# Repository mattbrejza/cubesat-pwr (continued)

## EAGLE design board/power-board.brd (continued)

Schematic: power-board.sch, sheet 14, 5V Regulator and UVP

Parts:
C104, C110: 10n; C0603
C105: 100n; C0603
C106: 10u; C1206
C107: 0.1u; C0603
C108: 3.3n; C0603
C109: 22u; C1210
L2: 2.2u; VISHAY-INDUCTOR
R102: 14.5k; R0603
R103: 10.2k; R0603
R104: 12.4k; R0603
R105: 124k; R0603
R106, R107: 100k; R0603
R108: 0; R0603
R141: 4.02k; R0603
TP14, TP20: PTR1TP09R; TP09R
U46: TLV3491AIDBV; SOT23-5
U47: TPS62133RGT; RGT.16
U48: FDS8858CZ; SO8

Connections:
GND: C104.2, C105.2, C106.2, C107.2, C108.1, C109.2, C110.2, R103.1, R105.1, U46.2 (V-), U47.5 (FB), U47.6 (AGND), U47.8 (DEF), U47.15 (PGND), U47.16 (PGND), U47.PAD (AGND), U48.1 (S); also elsewhere on the board
unnamed: C108.2, U47.9 (SS/TR)
unnamed: L2.1, U47.1 (SW), U47.2 (SW), U47.3 (SW)
unnamed: R107.2, R108.2, U48.4 (G)
unnamed: R102.2, R103.2, R141.1
unnamed: R106.1, R141.2, U46.3 (+IN)
unnamed: R108.1, U48.7 (D), U48.8 (D)
unnamed: R104.1, R105.2, U46.4 (-IN)
REG3V3: C105.1, R104.2, U46.5 (V+); also elsewhere on the board
REG5V: C109.1, C110.1, L2.2, R107.1, TP20.TP, U47.7 (FSW), U47.14 (VOS), U48.3 (S); also elsewhere on the board
UVP5V_GATE: R106.2, TP14.TP, U46.1 (OUT), U48.2 (G)
UVP5V_OUT: U48.5 (D), U48.6 (D); also elsewhere on the board
VBATT: C104.1, C106.1, C107.1, R102.1, U47.10 (AVIN), U47.11 (PVIN), U47.12 (PVIN), U47.13 (EN); also elsewhere on the board

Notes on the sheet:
Application circuits taken from TPS62130 Datasheet Fig. 44.
FSW = High for 1.25MHz operation. Connect FSW to VOUT or PG.
See Fig. 50 for layout
3A Buck Regulators
TLV3491 bypass
5V Regulator and UVP

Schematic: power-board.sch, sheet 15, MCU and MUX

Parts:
C111, C113: 0.1u; C0603K
C112: 1n; C0603K
R29, R30: 4k7; R0603
R109: 47k; R0603
U49: MSP430F2132; RHB32
U50: ADG732; LFCSP48
X1: 32.768k; CC7V-T1A

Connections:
BATT_I2C_SCL: R30.1, U49.11; also elsewhere on the board
BATT_I2C_SDA: R29.1, U49.10; also elsewhere on the board
CHARGE_CSENSE_MUX: U50.27 (S19); also elsewhere on the board
GND: C111.2, C112.2, C113.2, U49.1, U49.TP (33), U50.20 (!CS), U50.21 (!WR), U50.22 (!EN), U50.23 (GND), U50.24 (VSS), U50.EXP (GND); also elsewhere on the board
MCU_INT: U49.15; also elsewhere on the board
MCU_RX: U49.14; also elsewhere on the board
MCU_TX: U49.13; also elsewhere on the board
MPPT2_LOWER_PV_VSENSE: U50.30 (S22); also elsewhere on the board
MPPT2_MID_PV_VSENSE: U50.31 (S23); also elsewhere on the board
MPPT_BUS_VSENSE: U50.29 (S21); also elsewhere on the board
MSP-RST: C112.1, R109.1, U49.5; also elsewhere on the board
MSP-TEST: U49.29; also elsewhere on the board
MUX_A0: U49.32, U50.15 (A0)
MUX_A1: U49.18, U50.16 (A1)
MUX_A2: U49.8, U50.17 (A2)
MUX_A3: U49.7, U50.18 (A3)
MUX_A4: U49.6, U50.19 (A4)
MUX_OUT: U49.16, U50.43 (D)
unnamed: U49.2, X1.P$2 (2)
unnamed: U49.3, X1.P$1 (1)
OCP1_CSENSE_MUX: U50.38 (S30); also elsewhere on the board
OCP1_MCU_EN: U49.23; also elsewhere on the board
OCP1_VSENSE: U50.46 (S15); also elsewhere on the board
OCP2_CSENSE_MUX: U50.48 (S13); also elsewhere on the board
OCP2_MCU_EN: U49.22; also elsewhere on the board
OCP2_VSENSE: U50.47 (S14); also elsewhere on the board
OCP3_CSENSE_MUX: U50.4 (S9); also elsewhere on the board
OCP3_MCU_EN: U49.21; also elsewhere on the board
OCP3_VSENSE: U50.3 (S10); also elsewhere on the board
OCP4_CSENSE_MUX: U50.7 (S6); also elsewhere on the board
OCP4_MCU_EN: U49.26; also elsewhere on the board
OCP4_VSENSE: U50.6 (S7); also elsewhere on the board
OCP5_CSENSE_MUX: U50.10 (S3); also elsewhere on the board
OCP5_MCU_EN: U49.25; also elsewhere on the board
OCP5_VSENSE: U50.5 (S8); also elsewhere on the board
OCP6_CSENSE_MUX: U50.9 (S4); also elsewhere on the board
OCP6_MCU_EN: U49.24; also elsewhere on the board
OCP6_VSENSE: U50.8 (S5); also elsewhere on the board
PV_EAST1_CSENSE_MUX: U50.40 (S32); also elsewhere on the board
PV_EAST2_CSENSE_MUX: U50.39 (S31); also elsewhere on the board
PV_NORTH1_CSENSE_MUX: U50.26 (S18); also elsewhere on the board
PV_NORTH2_CSENSE_MUX: U50.25 (S17); also elsewhere on the board
PV_SOUTH1_CSENSE_MUX: U50.34 (S26); also elsewhere on the board
PV_SOUTH2_CSENSE_MUX: U50.33 (S25); also elsewhere on the board
PV_TOP1_CSENSE_MUX: U50.12 (S1); also elsewhere on the board
PV_TOP2_CSENSE_MUX: U50.11 (S2); also elsewhere on the board
PV_WEST1_CSENSE_MUX: U50.28 (S20); also elsewhere on the board
PV_WEST2_CSENSE_MUX: U50.32 (S24); also elsewhere on the board
SYS_3V3_CSENSE_MUX: U50.1 (S12); also elsewhere on the board
SYS_5V_CSENSE_MUX: U50.2 (S11); also elsewhere on the board
UVP3V3_OUT: C111.1, C113.1, R29.2, R30.2, R109.2, U49.30, U50.13 (VDD), U50.14 (VDD); also elsewhere on the board
UVP3V3_VSENSE: U50.36 (S28); also elsewhere on the board
UVP5V_VSENSE: U50.35 (S27); also elsewhere on the board
VBATT_VSENSE: U50.37 (S29); also elsewhere on the board

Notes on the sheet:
Decoupling
Microcontroller and Multiplexer

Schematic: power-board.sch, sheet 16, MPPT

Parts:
C114, C115, C122, C123, C145, C146, C150, C151, C155, C156, C160, C161: 10u; C0805K
C116, C117, C144, C149, C154, C159: 100n; C0603K
C118, C119, C143, C148, C153, C158: 1u; C0603K
C120, C121, C147, C152, C157, C162: 4.7u; C0805K
D7, D8, D12, D13, D14, D15: 5V1; SMBJ
L3, L4, L6, L7, L8, L9: 10uH; MSS7341
R110, R111, R112, R113, R114, R115, R118, R119, R143, R144, R145, R147, R148, R149, R151, R152, R153, R155: 1k; R0603
R116, R117, R142, R146, R150, R154: 10m; R1206
TP29, TP31, TP32, TP33, TP35: PTR1TP09R; TP09R
U51, U52, U55, U56, U57, U58: SPV1040T; TSSOP8

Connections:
CHARGE_IN: C122.1, C145.1, C155.1, R113.1, R116.1, R119.1, R142.1, R149.1, R150.1, TP31.TP; also elsewhere on the board
GND: C115.2, C117.2, C121.2, C123.2, C149.2, C150.2, C151.2, C152.2, C159.2, C160.2, C161.2, C162.2, D8.A, D13.A, D15.A, TP33.TP, U52.2 (GND), U52.5 (VCTRL), U56.2 (GND), U56.5 (VCTRL), U58.2 (GND), U58.5 (VCTRL); also elsewhere on the board
MPPT1H_PV_P: C114.1, L3.1, R110.1; also elsewhere on the board
MPPT1L_PV_P: C115.1, L4.1, R111.1; also elsewhere on the board
MPPT1_MID: C114.2, C116.2, C120.2, C122.2, C123.1, D7.A, R115.1, R117.1, TP29.TP, U51.2 (GND), U51.5 (VCTRL); also elsewhere on the board
MPPT2H_PV_P: C146.1, L6.1, R143.1; also elsewhere on the board
MPPT2L_PV_P: C151.1, L7.1, R147.1; also elsewhere on the board
MPPT2_MID: C144.2, C145.2, C146.2, C147.2, C150.1, D12.A, R145.1, R146.1, TP32.TP, U55.2 (GND), U55.5 (VCTRL); also elsewhere on the board
MPPT3H_PV_P: C156.1, L8.1, R151.1; also elsewhere on the board
MPPT3L_PV_P: C161.1, L9.1, R155.1; also elsewhere on the board
MPPT3_MID: C154.2, C155.2, C156.2, C157.2, C160.1, D14.A, R153.1, R154.1, TP35.TP, U57.2 (GND), U57.5 (VCTRL); also elsewhere on the board
unnamed: C118.1, R112.2, U51.7 (ICTRL+)
unnamed: C118.2, R113.2, U51.6 (ICTRL-)
unnamed: C120.1, D7.C, R112.1, R116.2, U51.4 (VOUT)
unnamed: C116.1, R110.2, U51.1 (MPP-SET), U51.8 (XSHUT)
unnamed: L3.2, U51.3 (LX)
unnamed: C143.1, R118.2, U55.7 (ICTRL+)
unnamed: C143.2, R119.2, U55.6 (ICTRL-)
unnamed: C147.1, D12.C, R118.1, R142.2, U55.4 (VOUT)
unnamed: C119.1, R114.2, U52.7 (ICTRL+)
unnamed: C119.2, R115.2, U52.6 (ICTRL-)
unnamed: C121.1, D8.C, R114.1, R117.2, U52.4 (VOUT)
unnamed: C117.1, R111.2, U52.1 (MPP-SET), U52.8 (XSHUT)
unnamed: L4.2, U52.3 (LX)
unnamed: C144.1, R143.2, U55.1 (MPP-SET), U55.8 (XSHUT)
unnamed: L6.2, U55.3 (LX)
unnamed: C148.1, R144.2, U56.7 (ICTRL+)
unnamed: C148.2, R145.2, U56.6 (ICTRL-)
unnamed: C152.1, D13.C, R144.1, R146.2, U56.4 (VOUT)
unnamed: C149.1, R147.2, U56.1 (MPP-SET), U56.8 (XSHUT)
unnamed: L7.2, U56.3 (LX)
unnamed: C153.1, R148.2, U57.7 (ICTRL+)
unnamed: C153.2, R149.2, U57.6 (ICTRL-)
unnamed: C157.1, D14.C, R148.1, R150.2, U57.4 (VOUT)
unnamed: C154.1, R151.2, U57.1 (MPP-SET), U57.8 (XSHUT)
unnamed: L8.2, U57.3 (LX)
unnamed: C158.1, R152.2, U58.7 (ICTRL+)
unnamed: C158.2, R153.2, U58.6 (ICTRL-)
unnamed: C162.1, D15.C, R152.1, R154.2, U58.4 (VOUT)
unnamed: C159.1, R155.2, U58.1 (MPP-SET), U58.8 (XSHUT)
unnamed: L9.2, U58.3 (LX)

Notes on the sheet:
MPPT
MPPT 1H
MPPT 1L
MPPT 2L
MPPT 3L
MPPT 3H
MPPT 2H
north/south
east/west
top

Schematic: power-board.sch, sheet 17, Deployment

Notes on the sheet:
Deployment power MOSFETs
I think this should be connected to the GND, not to RBF_A

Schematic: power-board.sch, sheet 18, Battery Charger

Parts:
C124: 2.2u; C1210
C125: C0603; P0603
C126, C127, C130, C139: 1.0u; P0805
C128, C141: 22p; P0603
C129, C132, C142: 0.1u; P0603
C131: 100n; P0603
C133, C140: 10u; C1210
C134: 1.0u; C0805
C135: C-EUC0603; C0603
C137: 10u; P1210
D9, D11: PDS1040; POWERDI5
D10: ZLLS350; SOD-523
L5: IHLP2525CZ
Q3: SI7288; SO8-POWERPAK_DUAL
R120, R121: 3.9; R0603
R122: 10.0k; P0603
R123: 30.1k; P0603
R124: 5.23k; P0603
R125: 100; P0603
R126, R130: 100k; P0603
R127: 10; P0805
R128, R133: R0805; P0805
R129: 698k; P0603
R131: 2.2; P0603
R134: 62m; R1206
R135, R137: 0; P0603
R138: 301k; P0603
R139: 102k; P0603
SH1, SH2: SHORT
U53: BQ24650_RVA_16; RVA16_2P14X2P14

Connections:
CHARGE_BATT: C142.1, R137.2; also elsewhere on the board
CHARGE_IN: C128.1, D9.LEFT (A1), D9.RIGHT (A2), R120.2, R121.2, R129.2; also elsewhere on the board
CHARGE_OUT: C137.1, C139.1, D11.LEFT (A1), D11.RIGHT (A2), R134.2, R135.2; also elsewhere on the board
GND: C124.2, C125.2, C126.2, C127.1, C130.2, C131.2, C133.2, C134.2, C137.2, C139.2, C140.2, C142.2, Q3.3 (S), R122.1, R123.1, R126.1, R130.1, R133.1, R139.1, SH1.1, SH1.2, SH2.1, SH2.2, U53.11 (GND), U53.17 (EPAD); also elsewhere on the board
MPPSET: C128.2, R129.1, R130.2, U53.2 (MPPSET)
unnamed: C141.1, R137.1, R138.2
unnamed: C124.1, R120.1, R121.1
unnamed: C135.2, R133.2
unnamed: C127.2, R127.1, R128.1, U53.1 (VCC)
unnamed: C130.1, D10.2 (A), U53.12 (REGN)
unnamed: C129.1, C131.1, L5.2, R134.1, U53.10 (SRP)
unnamed: C129.2, R135.1, U53.9 (SRN)
unnamed: C132.2, C135.1, L5.1, Q3.1 (S), Q3.5 (D2), Q3.PAD56 (D), U53.14 (PH)
unnamed: C132.1, D10.1 (C), R131.2
unnamed: R131.1, U53.16 (BTST)
unnamed: C141.2, R138.1, R139.2, U53.8 (VFB)
unnamed: R122.2, R123.2, R124.1, R125.1
unnamed: Q3.2 (G), U53.15 (HIDRV)
unnamed: Q3.4 (G), U53.13 (LODRV)
PROP: C133.1, C134.1, C140.1, D9.HEAT_SINK (C), D11.HEAT_SINK (C), Q3.8 (D2), Q3.PAD78 (D), R127.2, R128.2
TS: C125.1, R125.2, U53.4 (TS)
VREF: C126.1, R124.2, R126.2, U53.6 (VREF), U53.7 (TERM_EN)

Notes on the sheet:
Battery Charger
Allow separate GND planes to connect

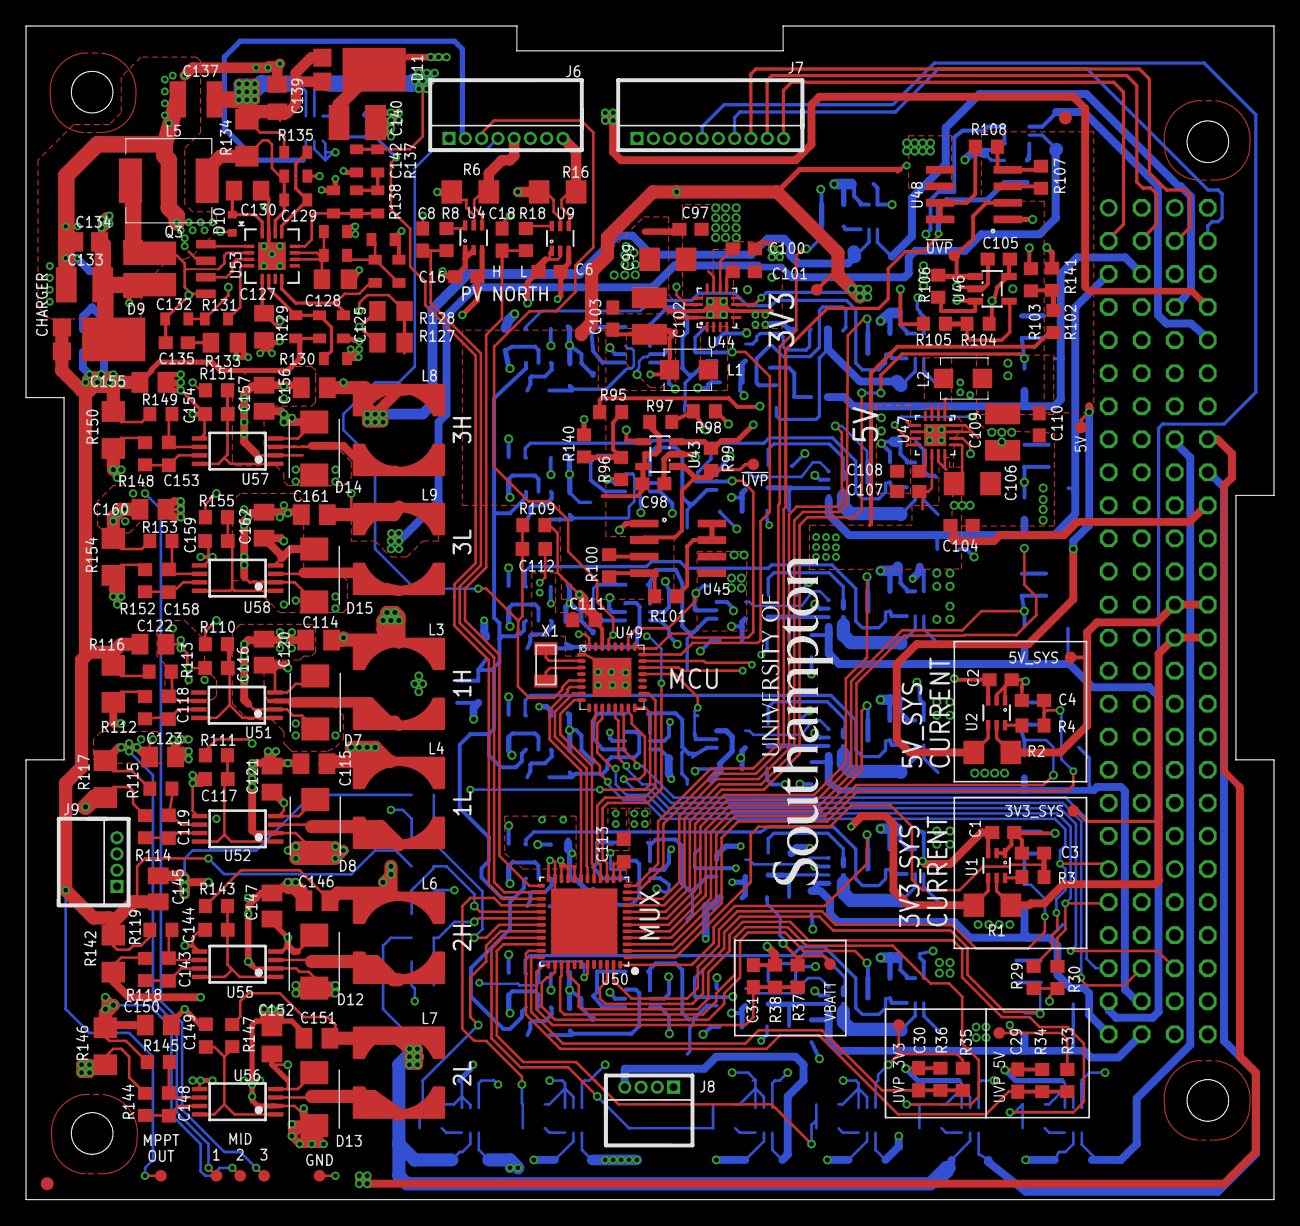
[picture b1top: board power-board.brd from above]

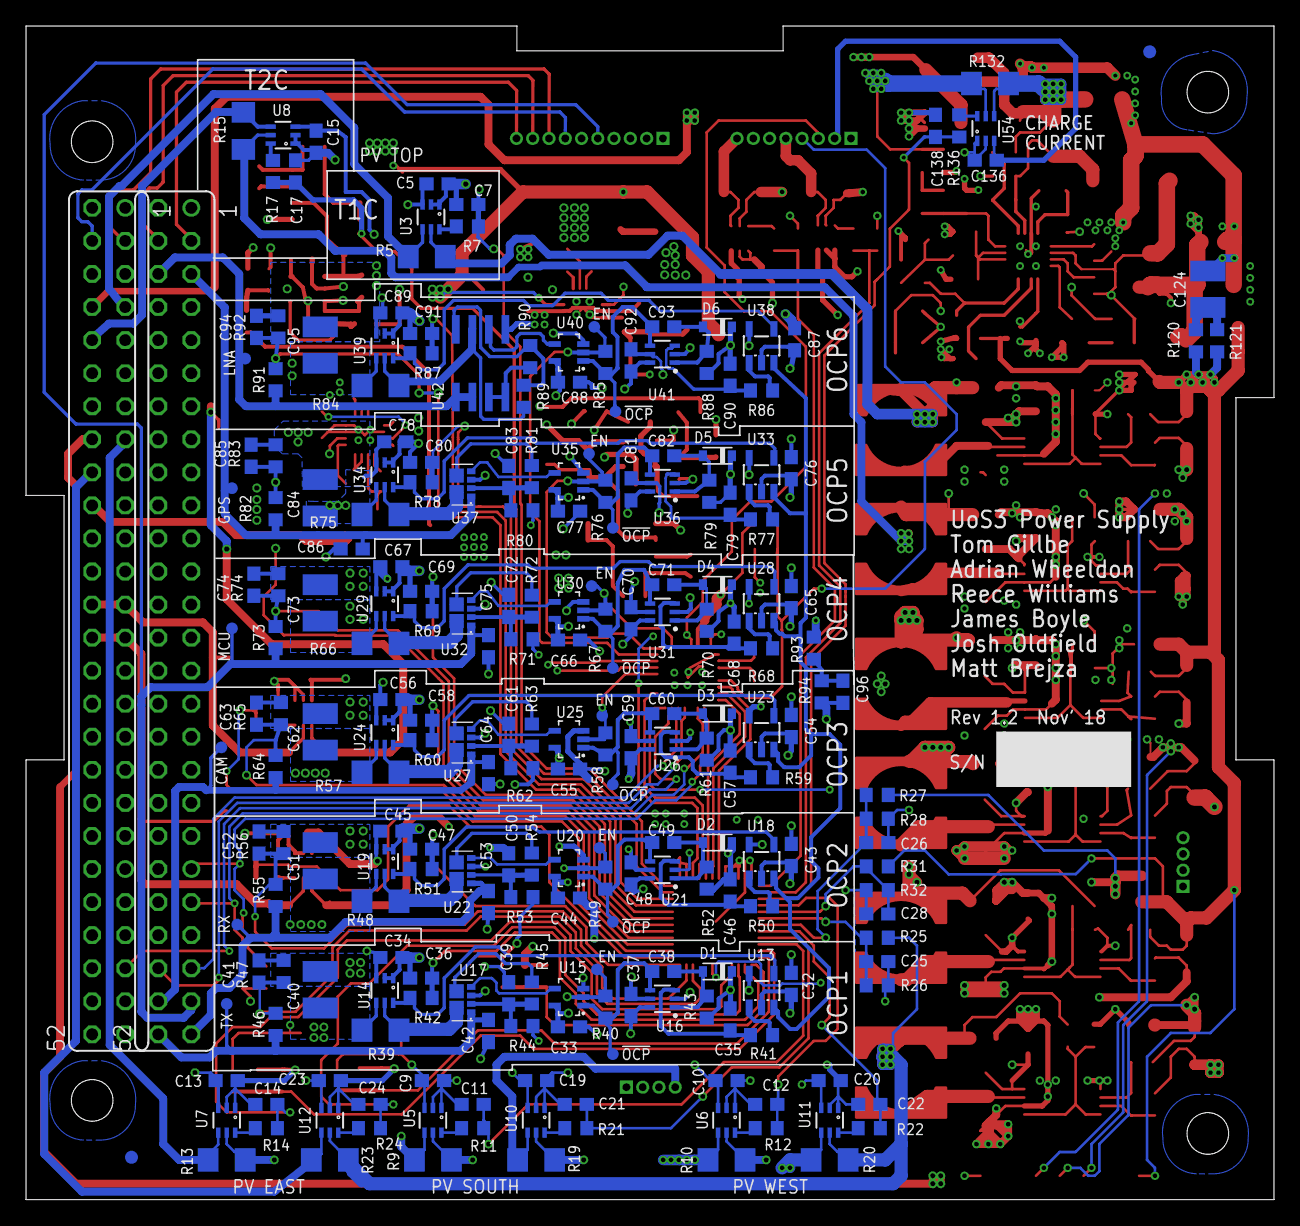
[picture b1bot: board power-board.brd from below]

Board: 4 copper layers, 95.9 x 90.2 mm, 445 parts (236 on the bottom side), 224 nets.

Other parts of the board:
U$1: UOS_LOGO_SML

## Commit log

2017-03-10 removing deployment switches, adding testpoints
2017-03-13 done (hopefully)
2018-02-24 committing WIP
2018-05-03 various bits of routing over a period of time
2018-05-07 some routing
2018-05-10 some more routing
2018-05-18 changing mppt voltage monitoring points
2018-05-19 no airwires
2018-07-01 separating vbat/charge. routing improvements for 3.3/5V regs
2018-07-01 updating component values
2018-11-04 adding i2c pullups
2018-11-04 fixing silk layer
2018-11-06 updated UVP componets to 7.2V/8V to match changes to the previous board. Also increased the UVP components by 10x to reduce current consumption
2018-11-06 adding gerbers
2019-03-07 updating component values (fixing prev errors)
